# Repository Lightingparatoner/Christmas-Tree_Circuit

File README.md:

# Christmas Tree
This is the circuit for Christmas tree. Uses PIC12F683 for controlling LEDs but any compatible µC can be used instead.

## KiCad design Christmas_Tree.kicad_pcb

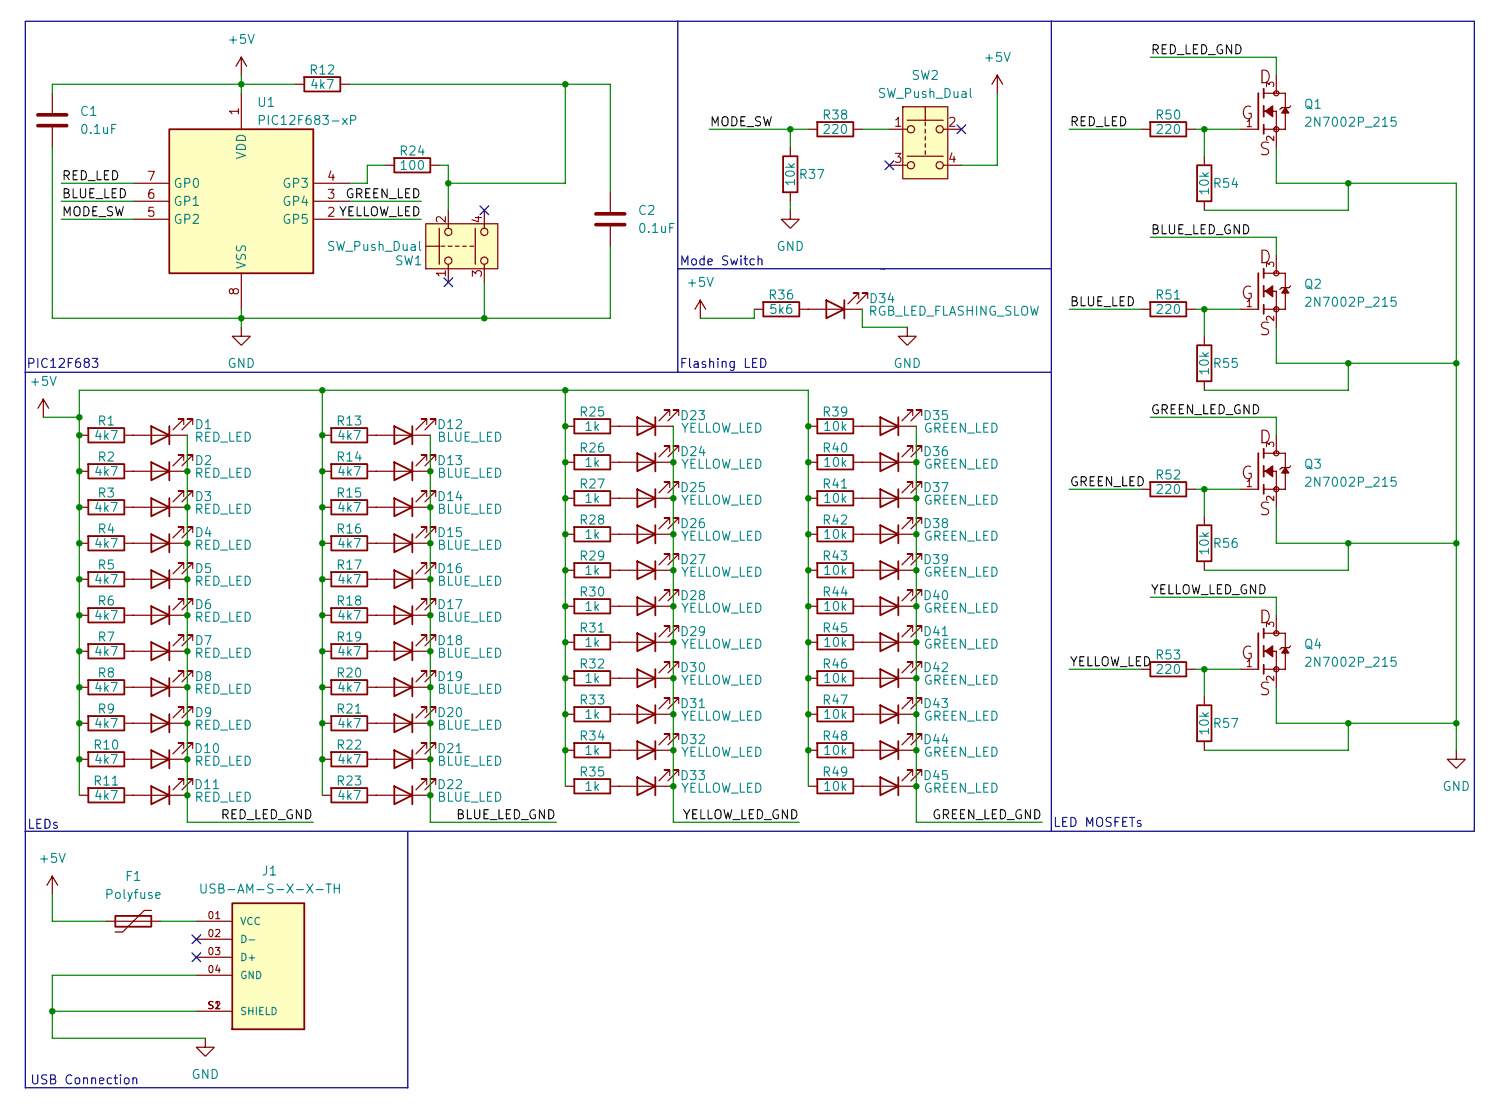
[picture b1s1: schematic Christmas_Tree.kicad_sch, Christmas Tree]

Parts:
C1, C2: 0.1uF; C_0603_1608Metric
D1, D2, D3, D4, D5, D6, D7, D8, D9, D10, D11: RED_LED; LED_D5.0mm
D12, D13, D14, D15, D16, D17, D18, D19, D20, D21, D22: BLUE_LED; LED_D5.0mm
D23, D24, D25, D26, D27, D28, D29, D30, D31, D32, D33: YELLOW_LED; LED_D5.0mm
D34: RGB_LED_FLASHING_SLOW; LED_D5.0mm
D35, D36, D37, D38, D39, D40, D41, D42, D43, D44, D45: GREEN_LED; LED_D5.0mm
F1: Polyfuse; RESC3216X125N
J1: USB-AM-S-X-X-TH; SAMTEC_USB-AM-S-X-X-TH; PARTREV U
Q1, Q2, Q3, Q4: 2N7002P_215; 2N7002P,215
R1, R2, R3, R4, R5, R6, R7, R8, R9, R10, R11, R12, R13, R14, R15, R16, R17, R18, R19, R20, R21, R22, R23: 4k7; R_0805_2012Metric
R24: 100; R_0402_1005Metric
R25, R26, R27, R28, R29, R30, R31, R32, R33, R34, R35: 1k; R_0805_2012Metric
R36: 5k6; R_0805_2012Metric
R37, R54, R55, R56, R57: 10k; R_0402_1005Metric
R38, R50, R51, R52, R53: 220; R_0402_1005Metric
R39, R40, R41, R42, R43, R44, R45, R46, R47, R48, R49: 10k; R_0805_2012Metric
SW1, SW2: SW_Push_Dual; SW_PUSH_6mm_4pin
U1: PIC12F683-xP; DIP-8_W7.62mm

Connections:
+5V: C1.1, F1.2, R1.2, R2.2, R3.2, R4.2, R5.2, R6.2, R7.2, R8.2, R9.2, R10.2, R11.2, R12.2, R13.2, R14.2, R15.2, R16.2, R17.2, R18.2, R19.2, R20.2, R21.2, R22.2, R23.2, R25.2, R26.2, R27.2, R28.2, R29.2, R30.2, R31.2, R32.2, R33.2, R34.2, R35.2, R36.2, R39.2, R40.2, R41.2, R42.2, R43.2, R44.2, R45.2, R46.2, R47.2, R48.2, R49.2, SW2.4, U1.1 (VDD)
/BLUE_LED: R51.2, U1.6 (GP1)
/BLUE_LED_GND: D12.1 (K), D13.1 (K), D14.1 (K), D15.1 (K), D16.1 (K), D17.1 (K), D18.1 (K), D19.1 (K), D20.1 (K), D21.1 (K), D22.1 (K), Q2.3
/GREEN_LED: R52.2, U1.3 (GP4)
/GREEN_LED_GND: D35.1 (K), D36.1 (K), D37.1 (K), D38.1 (K), D39.1 (K), D40.1 (K), D41.1 (K), D42.1 (K), D43.1 (K), D44.1 (K), D45.1 (K), Q3.3
/MODE_SW: R37.1, R38.2, U1.5 (GP2)
/RED_LED: R50.2, U1.7 (GP0)
/RED_LED_GND: D1.1 (K), D2.1 (K), D3.1 (K), D4.1 (K), D5.1 (K), D6.1 (K), D7.1 (K), D8.1 (K), D9.1 (K), D10.1 (K), D11.1 (K), Q1.3
/YELLOW_LED: R53.2, U1.2 (GP5)
/YELLOW_LED_GND: D23.1 (K), D24.1 (K), D25.1 (K), D26.1 (K), D27.1 (K), D28.1 (K), D29.1 (K), D30.1 (K), D31.1 (K), D32.1 (K), D33.1 (K), Q4.3
GND: C1.2, C2.2, D34.1 (K), J1.04 (GND), J1.S1 (SHIELD), J1.S2 (SHIELD), Q1.2, Q2.2, Q3.2, Q4.2, R37.2, R54.2, R55.2, R56.2, R57.2, SW1.3, U1.8 (VSS)
unnamed: C2.1, R12.1, R24.1, SW1.2
unnamed: D1.2 (A), R1.1
unnamed: D2.2 (A), R2.1
unnamed: D3.2 (A), R3.1
unnamed: D4.2 (A), R4.1
unnamed: D5.2 (A), R5.1
unnamed: D6.2 (A), R6.1
unnamed: D7.2 (A), R7.1
unnamed: D8.2 (A), R8.1
unnamed: D9.2 (A), R9.1
unnamed: D10.2 (A), R10.1
unnamed: D11.2 (A), R11.1
unnamed: D12.2 (A), R13.1
unnamed: D13.2 (A), R14.1
unnamed: D14.2 (A), R15.1
unnamed: D15.2 (A), R16.1
unnamed: D16.2 (A), R17.1
unnamed: D17.2 (A), R18.1
unnamed: D18.2 (A), R19.1
unnamed: D19.2 (A), R20.1
unnamed: D20.2 (A), R21.1
unnamed: D21.2 (A), R22.1
unnamed: D22.2 (A), R23.1
unnamed: D23.2 (A), R25.1
unnamed: D24.2 (A), R26.1
unnamed: D25.2 (A), R27.1
unnamed: D26.2 (A), R28.1
unnamed: D27.2 (A), R29.1
unnamed: D28.2 (A), R30.1
unnamed: D29.2 (A), R31.1
unnamed: D30.2 (A), R32.1
unnamed: D31.2 (A), R33.1
unnamed: D32.2 (A), R34.1
unnamed: D33.2 (A), R35.1
unnamed: D34.2 (A), R36.1
unnamed: D35.2 (A), R39.1
unnamed: D36.2 (A), R40.1
unnamed: D37.2 (A), R41.1
unnamed: D38.2 (A), R42.1
unnamed: D39.2 (A), R43.1
unnamed: D40.2 (A), R44.1
unnamed: D41.2 (A), R45.1
unnamed: D42.2 (A), R46.1
unnamed: D43.2 (A), R47.1
unnamed: D44.2 (A), R48.1
unnamed: D45.2 (A), R49.1
unnamed: F1.1, J1.01 (VCC)
unnamed: Q1.1, R50.1, R54.1
unnamed: Q2.1, R51.1, R55.1
unnamed: Q3.1, R52.1, R56.1
unnamed: Q4.1, R53.1, R57.1
unnamed: R38.1, SW2.1
unnamed: R24.2, U1.4 (GP3)

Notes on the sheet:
LEDs
Flashing LED
PIC12F683
Mode Switch
USB Connection
LED MOSFETs

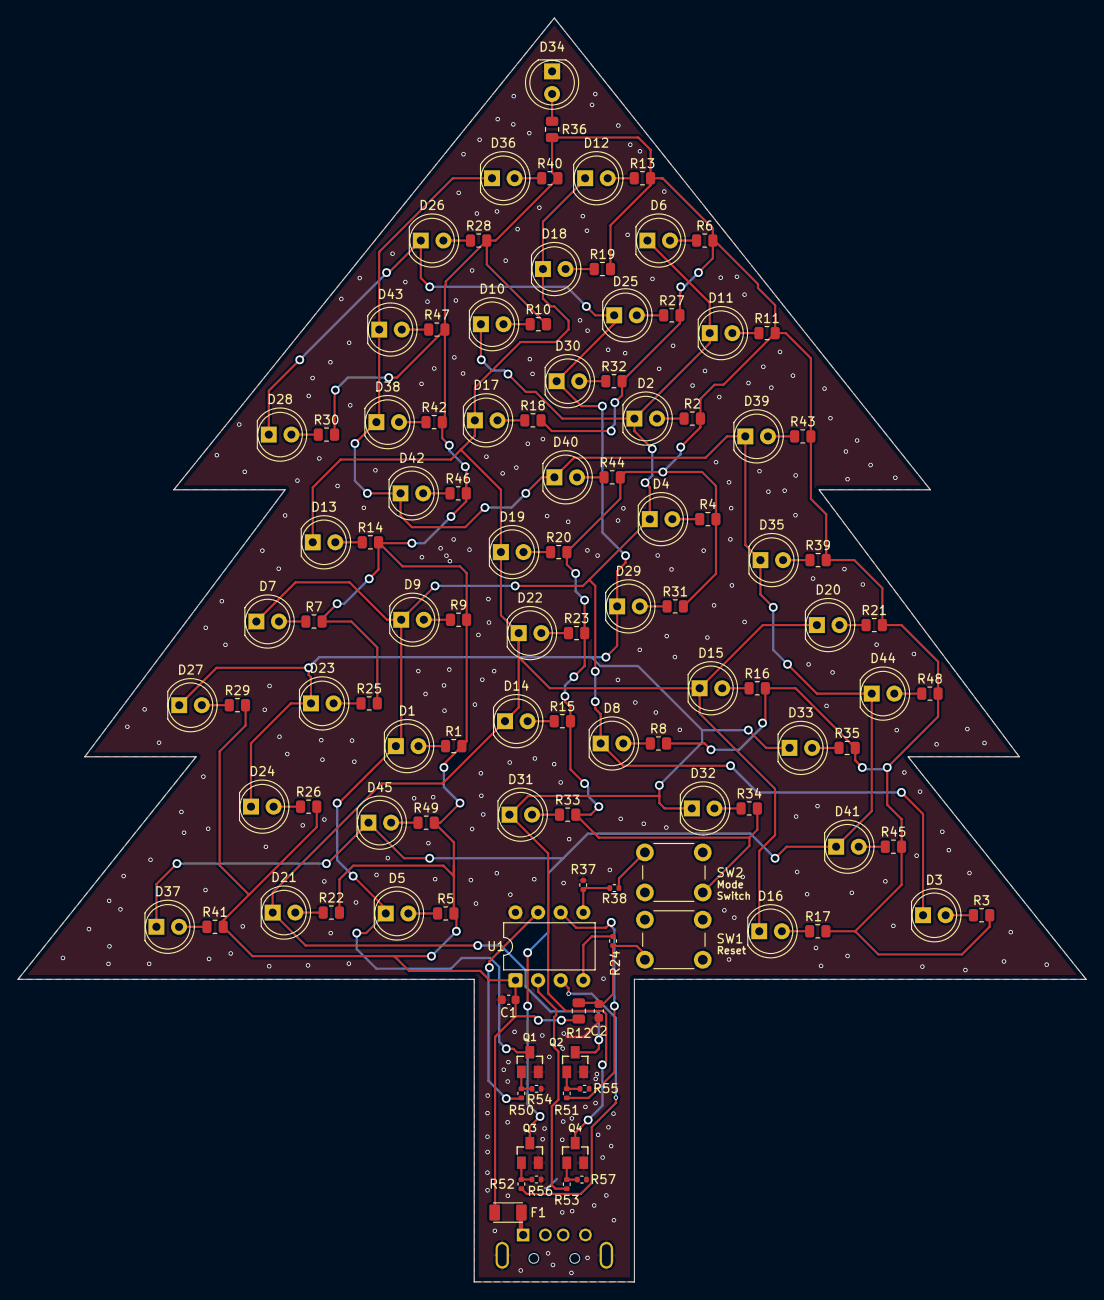
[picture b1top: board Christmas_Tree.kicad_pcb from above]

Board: 2 copper layers, 120.0 x 142.0 mm, 113 parts (1 on the bottom side), 64 nets.

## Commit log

2025-08-04 Create LICENSE
